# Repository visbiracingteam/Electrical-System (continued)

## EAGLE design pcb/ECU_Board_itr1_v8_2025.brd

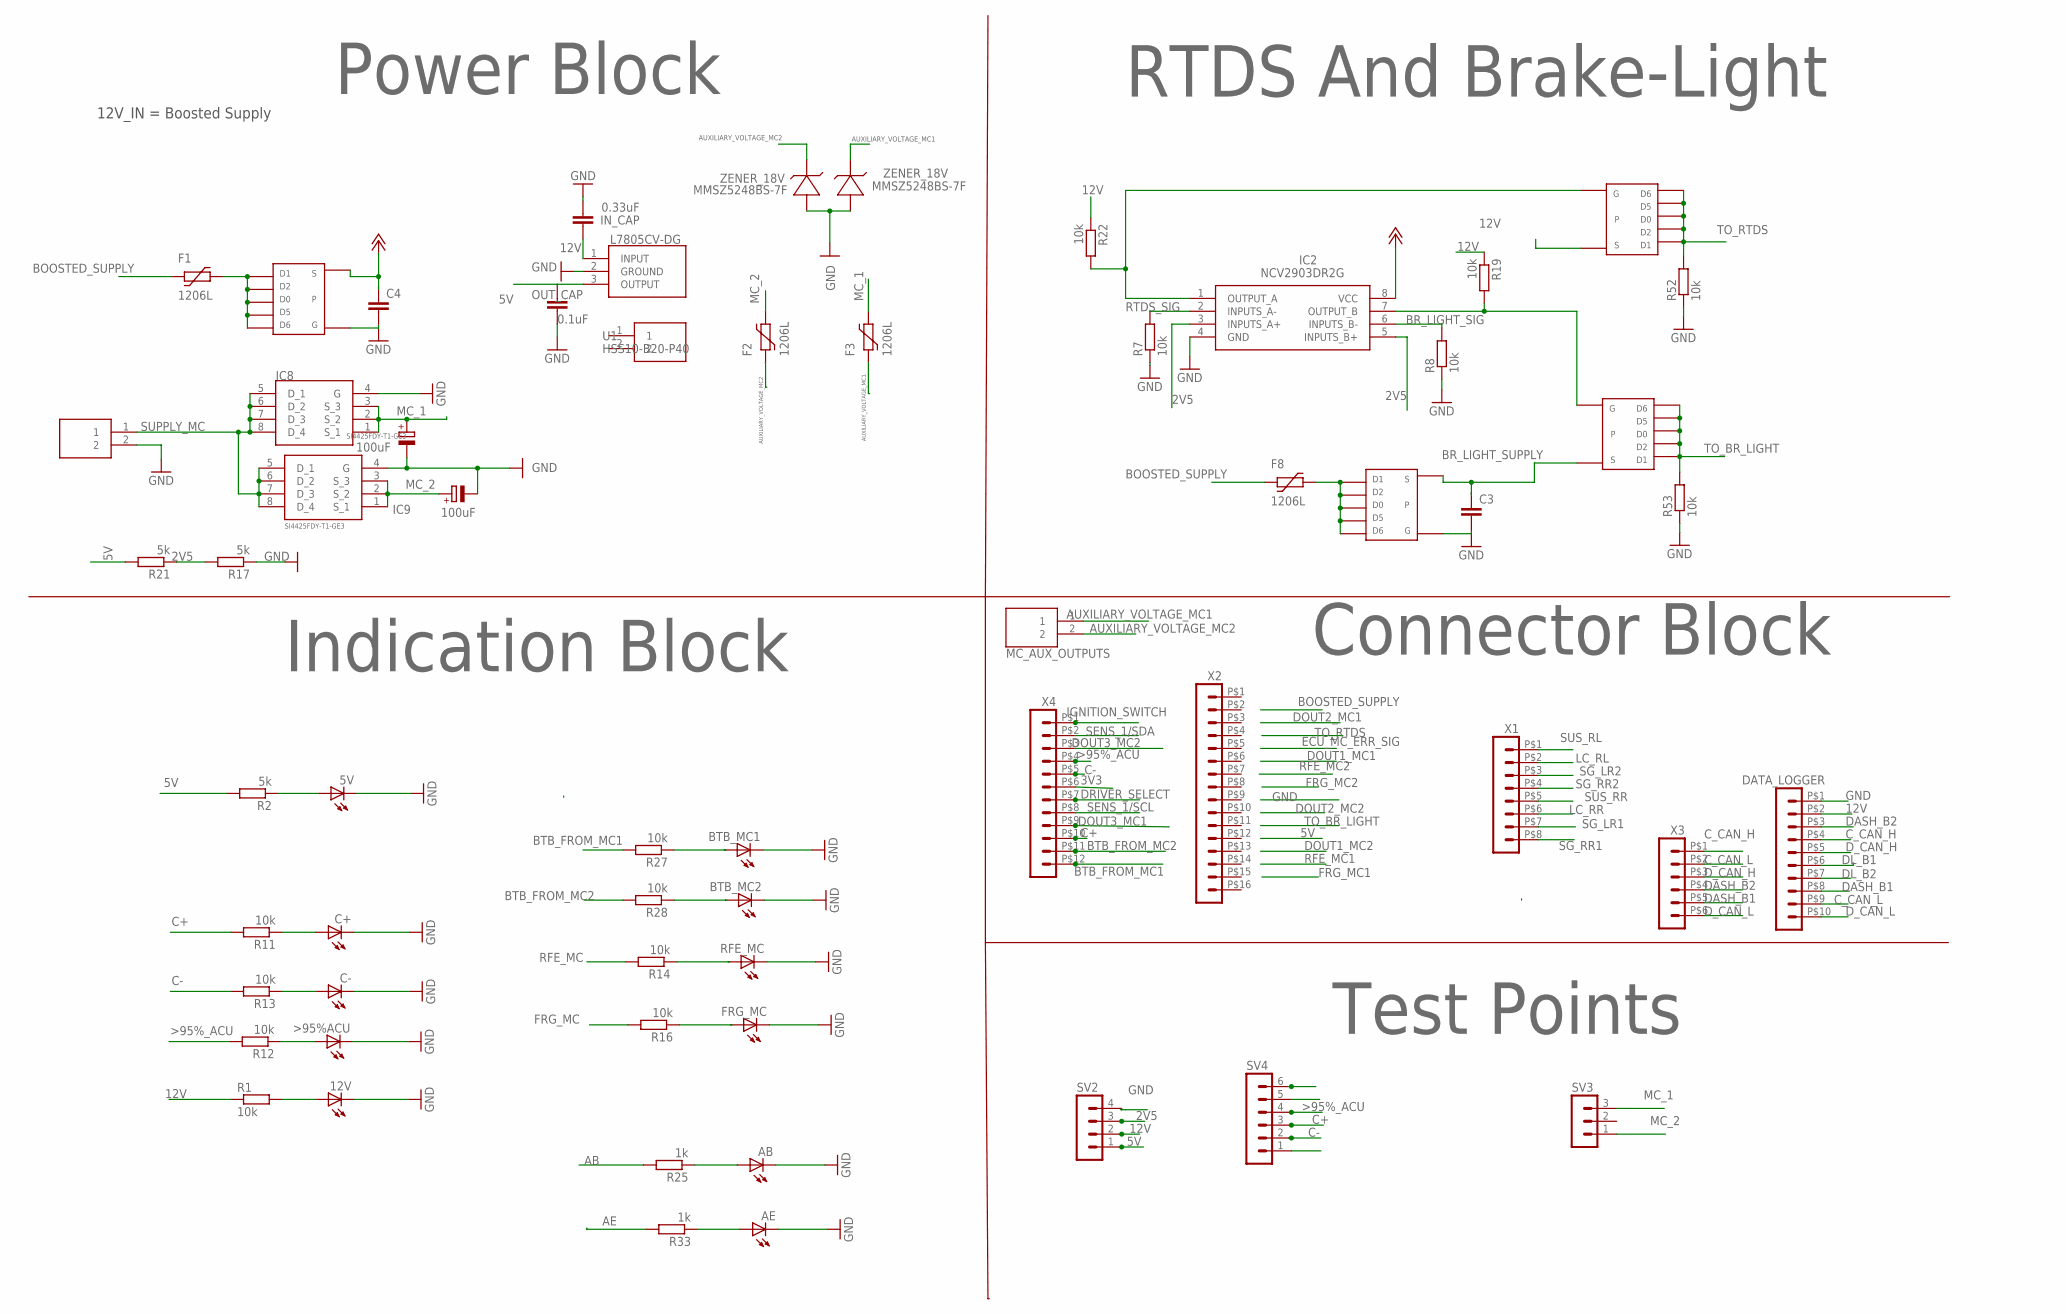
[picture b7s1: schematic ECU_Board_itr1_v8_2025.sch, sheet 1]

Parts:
5V, 12V: LED-FKIT-1206; FKIT-LED-1206
>95%ACU: LED-FKIT-1206; FKIT-LED-1206
AB: LED-FKIT-1206; FKIT-LED-1206
AE: LED-FKIT-1206; FKIT-LED-1206
BOOSTED_SUPPLY1: 172447-0002; 172447-YY02
BTB_MC1, BTB_MC2: LED-FKIT-1206; FKIT-LED-1206
C3, C4: C-EUC0805; C0805
C7, C8: 100uF; E2,5-6
C+: LED-FKIT-1206; FKIT-LED-1206
C-: LED-FKIT-1206; FKIT-LED-1206
D4, D5: ZENER; SOD123
DATA_LOGGER: HEADER_POS10_43045-1012; 43045-1012
F1, F2, F3, F8: 1206L
FRG_MC: LED-FKIT-1206; FKIT-LED-1206
IC2: NCV2903DR2G; SOIC127P600X175-8N
IC4: L7805CV-DG; TO255P460X1020X2008-3P
IC8, IC9: SI4425FDY-T1-GE3; SOIC127P600X175-8N
IN_CAP: 0.33uF; C0805
MC_AUX_OUTPUTS: 172447-0002; 172447-YY02
OUT_CAP: 0.1uF; C0805
R1, R7, R8, R11, R12, R13, R14, R16, R19, R22, R27, R28, R52, R53: 10k; R0805
R2, R17, R21: 5k; R0805
R25, R33: 1k; R0805
RFE_MC: LED-FKIT-1206; FKIT-LED-1206
SV2: MA04-1
SV3: MA03-1
SV4: MA06-1
U1: HSS10-B20-P40; HSS10B20P40
U$1, U$13, U$16, U$17: TSOP-6_PMOS
X1: HEADER_POS8_44769-0801; 44769-0801
X2: HEADER_POS16_44769-1601; 44769-1601
X3: HEADER_POS6_43045-0612; 43045-0612
X4: HEADER_POS12_44769-1201; 44769-1201

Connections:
2V5: IC2.3 (INPUTS_A+), IC2.5 (INPUTS_B+), R17.2, R21.1, SV2.3; also elsewhere on the board
3V3: SV4.1, X4.P$6 (6); also elsewhere on the board
5V: IC4.3 (OUTPUT), OUT_CAP.1, R2.2, R21.2, SV2.1; also elsewhere on the board
12V: C4.1, DATA_LOGGER.P$2 (2), IC2.8 (VCC), IC4.1 (INPUT), IN_CAP.1, R1.1, R19.1, R22.1, SV2.2, U$13.S, U$16.S; also elsewhere on the board
>95%_ACU: R12.2, SV4.4, X4.P$4 (4); also elsewhere on the board
AB: R25.2; also elsewhere on the board
AE: R33.2; also elsewhere on the board
AUXILIARY_VOLTAGE_MC1: D4.C (-), F3.P$1 (1), MC_AUX_OUTPUTS.1
AUXILIARY_VOLTAGE_MC2: D5.C (-), F2.P$1 (1), MC_AUX_OUTPUTS.2
BOOSTED_SUPPLY: F1.P$1 (1), F8.P$1 (1)
BR_LIGHT_SIG: IC2.6 (INPUTS_B-), R8.2; also elsewhere on the board
BR_LIGHT_SUPPLY: C3.1, U$1.S, U$17.S
BTB_FROM_MC1: R27.2, X4.P$12 (12); also elsewhere on the board
BTB_FROM_MC2: R28.2, X4.P$11 (11); also elsewhere on the board
C+: R11.2, SV4.3, X4.P$10 (10); also elsewhere on the board
C-: R13.2, SV4.2, X4.P$5 (5); also elsewhere on the board
C_CAN_H: DATA_LOGGER.P$4 (4), X3.P$1 (1); also elsewhere on the board
C_CAN_L: DATA_LOGGER.P$9 (9), X3.P$2 (2); also elsewhere on the board
DASH_B1: DATA_LOGGER.P$8 (8), X3.P$5 (5)
DASH_B2: DATA_LOGGER.P$3 (3), X3.P$4 (4)
DL_B1: DATA_LOGGER.P$6 (6); also elsewhere on the board
DL_B2: DATA_LOGGER.P$7 (7); also elsewhere on the board
DOUT3_MC1: SV4.5, X4.P$9 (9); also elsewhere on the board
DOUT3_MC2: SV4.6, X4.P$3 (3); also elsewhere on the board
DRIVER_SELECT: X4.P$7 (7); also elsewhere on the board
D_CAN_H: DATA_LOGGER.P$5 (5), X3.P$3 (3); also elsewhere on the board
D_CAN_L: DATA_LOGGER.P$10 (10), X3.P$6 (6); also elsewhere on the board
FRG_MC: R16.2; also elsewhere on the board
GND: 5V.C, 12V.C, >95%ACU.C, AB.C, AE.C, BOOSTED_SUPPLY1.2, BTB_MC1.C, BTB_MC2.C, C3.2, C4.2, C7.-, C8.-, C+.C, C-.C, D4.A (+), D5.A (+), DATA_LOGGER.P$1 (1), FRG_MC.C, IC2.4 (GND), IC4.2 (GROUND), IC8.4 (G), IC9.4 (G), IN_CAP.2, OUT_CAP.2, R7.1, R8.1, R17.1, R52.1, R53.1, RFE_MC.C, SV2.4, U$1.G, U$13.G; also elsewhere on the board
IGNITION_SWITCH: X4.P$1 (1); also elsewhere on the board
LC_RL: X1.P$2 (2); also elsewhere on the board
LC_RR: X1.P$6 (6); also elsewhere on the board
MC_1: C7.+, F3.P$2 (2), IC8.1 (S_1), IC8.2 (S_2), IC8.3 (S_3), SV3.3
MC_2: C8.+, F2.P$2 (2), IC9.1 (S_1), IC9.2 (S_2), IC9.3 (S_3), SV3.1
unnamed: 12V.A, R1.2
unnamed: R14.1, RFE_MC.A
unnamed: AB.A, R25.1
unnamed: FRG_MC.A, R16.1
unnamed: IC2.1 (OUTPUT_A), R22.2, U$16.G
unnamed: 5V.A, R2.1
unnamed: IC2.7 (OUTPUT_B), R19.2, U$17.G
unnamed: AE.A, R33.1
unnamed: F8.P$2 (2), U$1.1, U$1.2, U$1.5, U$1.6, U$1.D (D0)
unnamed: C+.A, R11.1
unnamed: >95%ACU.A, R12.1
unnamed: C-.A, R13.1
unnamed: BTB_MC1.A, R27.1
unnamed: BTB_MC2.A, R28.1
unnamed: F1.P$2 (2), U$13.1, U$13.2, U$13.5, U$13.6, U$13.D (D0)
RFE_MC: R14.2; also elsewhere on the board
RTDS_SIG: IC2.2 (INPUTS_A-), R7.2; also elsewhere on the board
SENS_1/SCL: X4.P$8 (8); also elsewhere on the board
SENS_1/SDA: X4.P$2 (2); also elsewhere on the board
SG_LR1: X1.P$7 (7); also elsewhere on the board
SG_LR2: X1.P$3 (3); also elsewhere on the board
SG_RR1: X1.P$8 (8); also elsewhere on the board
SG_RR2: X1.P$4 (4); also elsewhere on the board
SUPPLY_MC: BOOSTED_SUPPLY1.1, IC8.5 (D_1), IC8.6 (D_2), IC8.7 (D_3), IC8.8 (D_4), IC9.5 (D_1), IC9.6 (D_2), IC9.7 (D_3), IC9.8 (D_4)
SUS_RL: X1.P$1 (1); also elsewhere on the board
SUS_RR: X1.P$5 (5); also elsewhere on the board
TO_BR_LIGHT: R53.2, U$17.1, U$17.2, U$17.5, U$17.6, U$17.D (D0)
TO_RTDS: R52.2, U$16.1, U$16.2, U$16.5, U$16.6, U$16.D (D0)

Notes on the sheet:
Power Block
RTDS And Brake-Light
Indication Block
Connector Block
Test Points
12V_IN = Boosted Supply

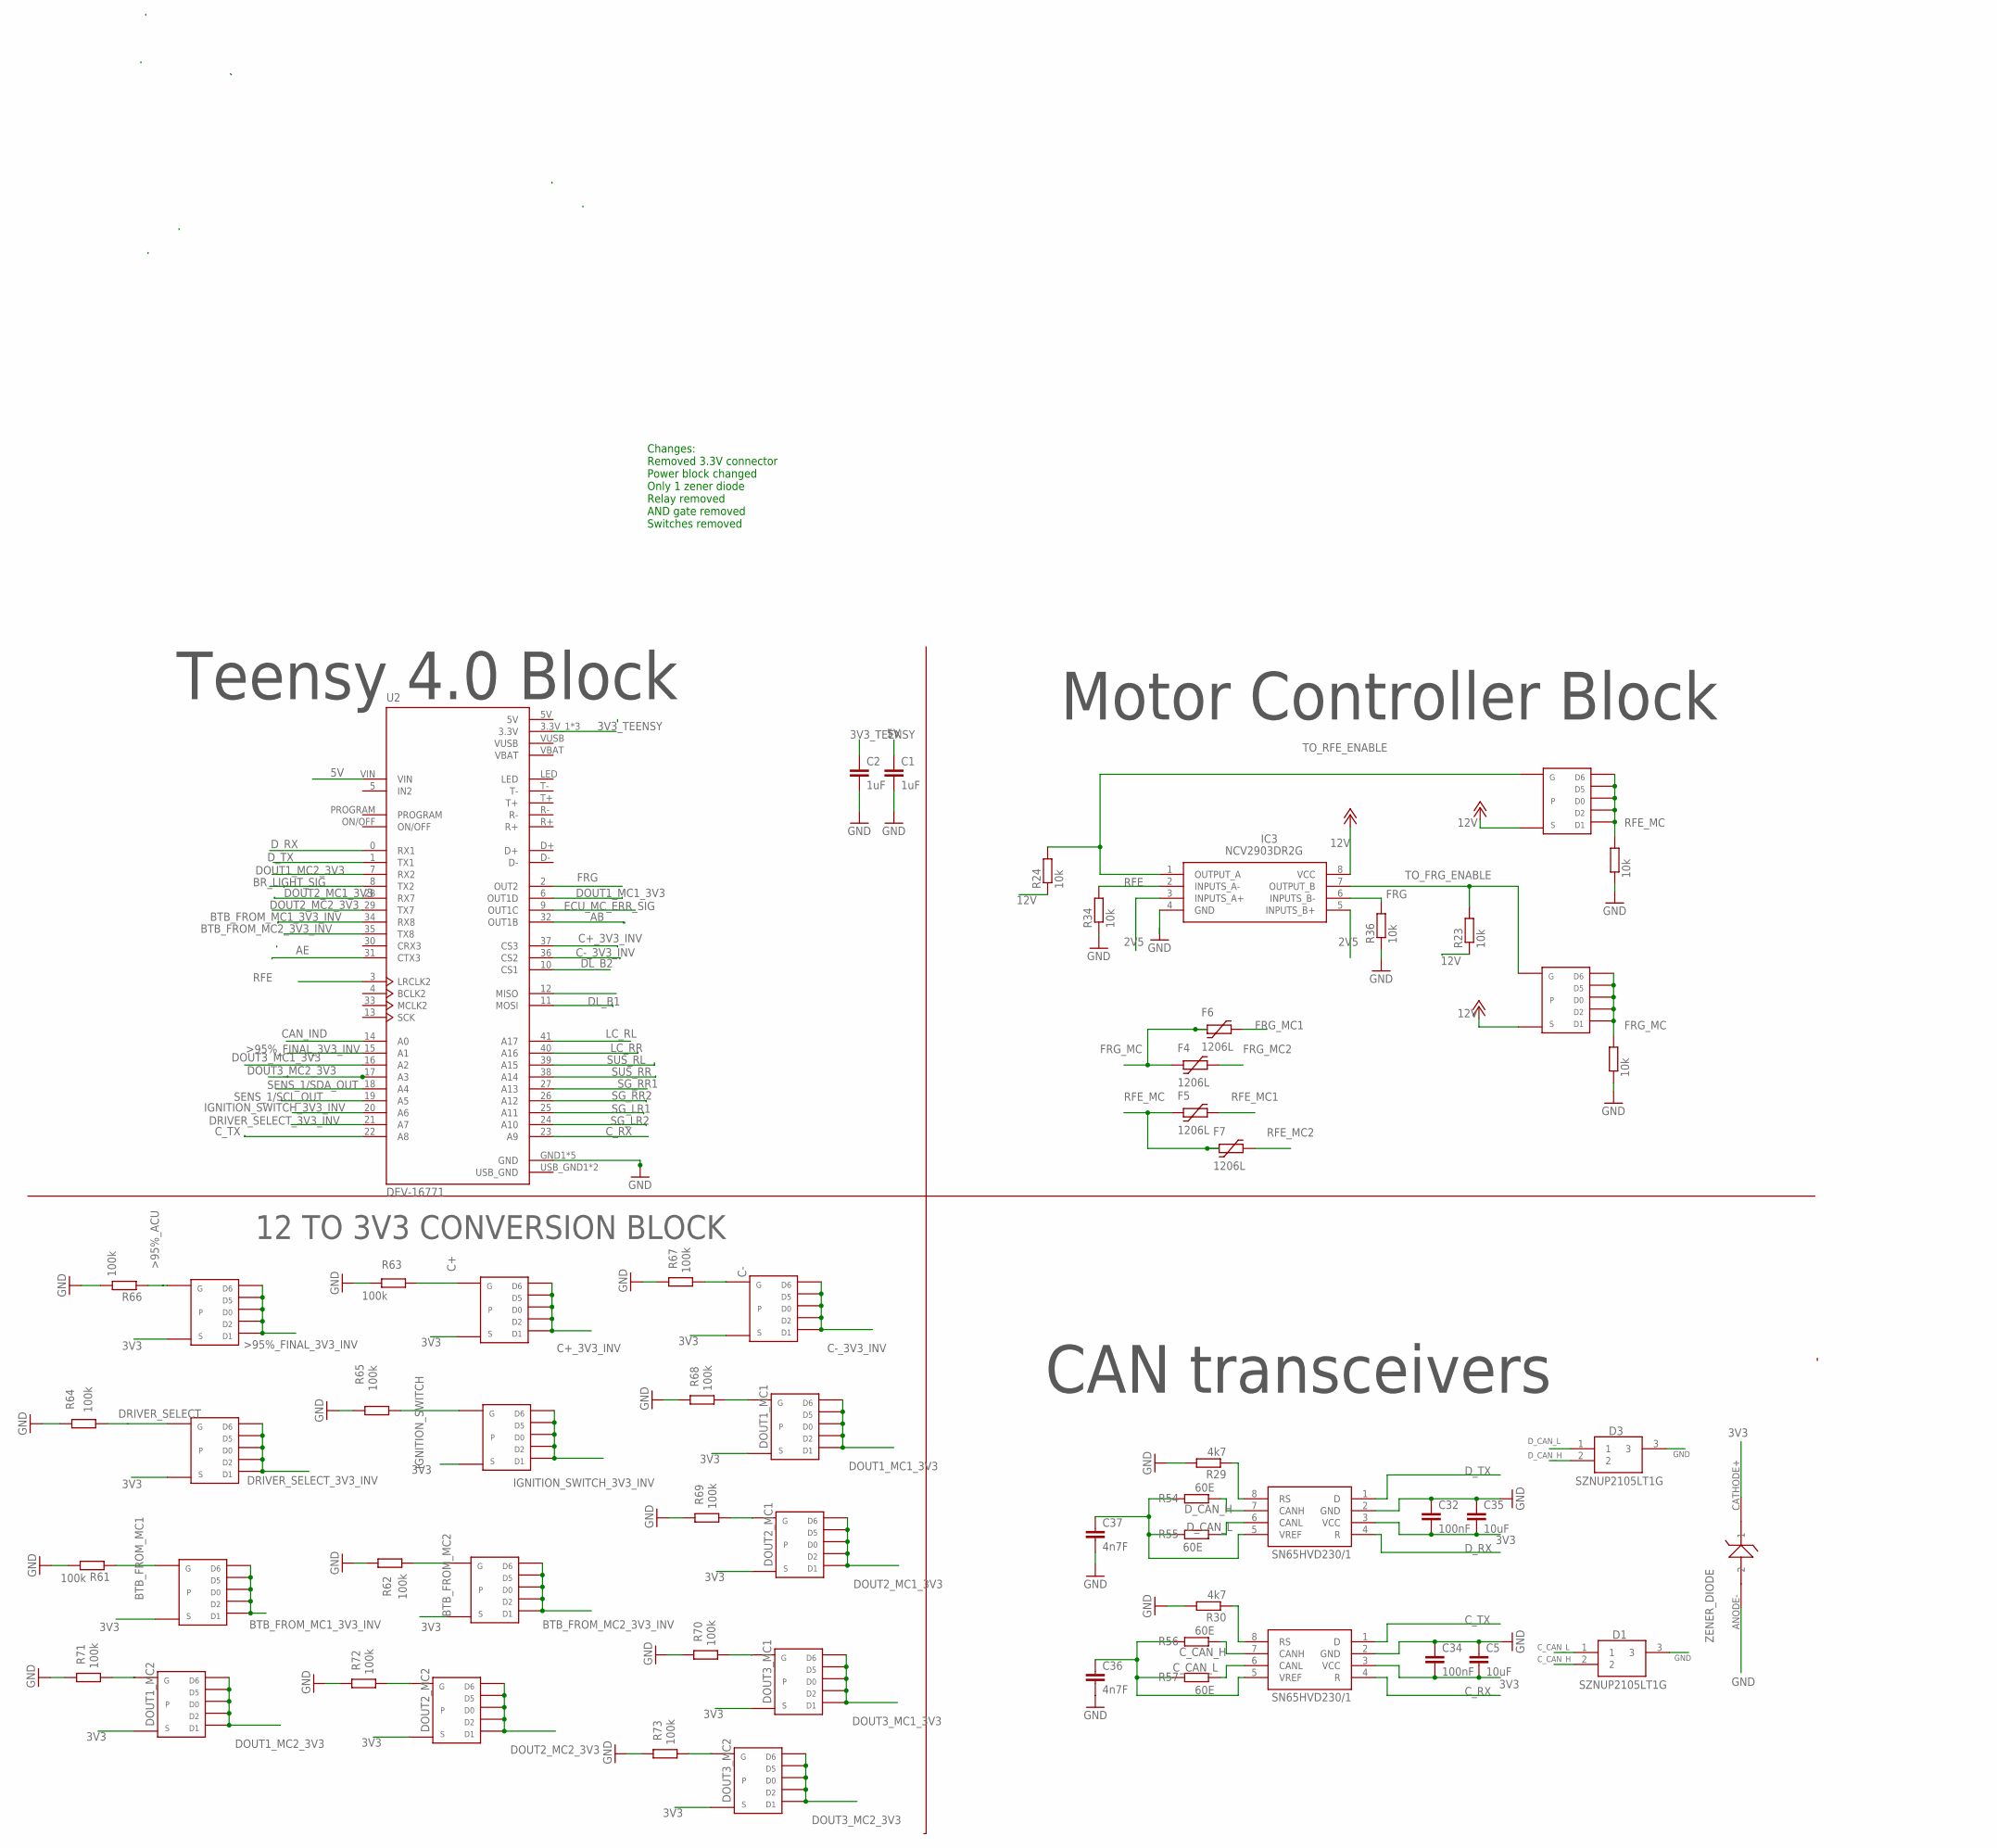
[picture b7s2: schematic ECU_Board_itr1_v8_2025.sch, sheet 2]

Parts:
C1, C2: 1uF; C0805
C5, C35: 10uF; C0805
C32, C34: 100nF; C0805
C36, C37: 4n7F; C0805
D1, D3: SZNUP2105LT1G; SOT96P237X111-3N
F4, F5, F6, F7: 1206L
IC3: NCV2903DR2G; SOIC127P600X175-8N
R23, R24, R31, R32, R34, R36: 10k; R0805
R29, R30: 4k7; R0805
R54, R55, R56, R57: 60E; R0805
R61, R62, R63, R64, R65, R66, R67, R68, R69, R70, R71, R72, R73: 100k; R0805
U2: DEV-16771; MODULE_DEV-16771
U$7, U$8: SN65HVD230/1; SO8
U$14, U$15, U$24, U$25, U$26, U$27, U$28, U$29, U$30, U$31, U$32, U$33, U$34, U$35, U$36: TSOP-6_PMOS
U$20: ZENER_DIODE; SOD323HE

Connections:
2V5: IC3.3 (INPUTS_A+), IC3.5 (INPUTS_B+); also elsewhere on the board
3V3: C5.2, C32.2, C34.2, C35.2, U$7.3 (VCC), U$8.3 (VCC), U$20.CATHODE+ (1), U$24.S, U$25.S, U$26.S, U$27.S, U$28.S, U$29.S, U$30.S, U$31.S, U$32.S, U$33.S, U$34.S, U$35.S, U$36.S; also elsewhere on the board
3V3_TEENSY: C2.1, U2.3.3V_1 (3.3V), U2.3.3V_2 (3.3V), U2.3.3V_3 (3.3V); also elsewhere on the board
5V: C1.1, U2.5V, U2.VIN; also elsewhere on the board
12V: IC3.8 (VCC), R23.1, R24.1, U$14.S, U$15.S; also elsewhere on the board
>95%_ACU: R66.1, U$25.G; also elsewhere on the board
>95%_FINAL_3V3_INV: U2.15 (A1), U$25.1, U$25.2, U$25.5, U$25.6, U$25.D (D0)
AB: U2.32 (OUT1B); also elsewhere on the board
AE: U2.31 (CTX3); also elsewhere on the board
BR_LIGHT_SIG: U2.8 (TX2); also elsewhere on the board
BTB_FROM_MC1: R61.1, U$27.G; also elsewhere on the board
BTB_FROM_MC1_3V3_INV: U2.34 (RX8), U$27.1, U$27.2, U$27.5, U$27.6, U$27.D (D0)
BTB_FROM_MC2: R62.1, U$26.G; also elsewhere on the board
BTB_FROM_MC2_3V3_INV: U2.35 (TX8), U$26.1, U$26.2, U$26.5, U$26.6, U$26.D (D0)
C+: R63.1, U$24.G; also elsewhere on the board
C+_3V3_INV: U2.37 (CS3), U$24.1, U$24.2, U$24.5, U$24.6, U$24.D (D0)
C-: R67.1, U$30.G; also elsewhere on the board
C-_3V3_INV: U2.36 (CS2), U$30.1, U$30.2, U$30.5, U$30.6, U$30.D (D0)
CAN_IND: U2.14 (A0)
C_CAN_H: D1.2, R56.1, U$7.7 (CANH); also elsewhere on the board
C_CAN_L: D1.1, R57.1, U$7.6 (CANL); also elsewhere on the board
C_RX: U2.23 (A9), U$7.4 (R)
C_TX: U2.22 (A8), U$7.1 (D)
DL_B1: U2.11 (MOSI); also elsewhere on the board
DL_B2: U2.10 (CS1); also elsewhere on the board
DOUT1_MC1: R68.1, U$31.G
DOUT1_MC1_3V3: U2.6 (OUT1D), U$31.1, U$31.2, U$31.5, U$31.6, U$31.D (D0)
DOUT1_MC2: R71.1, U$34.G
DOUT1_MC2_3V3: U2.7 (RX2), U$34.1, U$34.2, U$34.5, U$34.6, U$34.D (D0)
DOUT2_MC1: R69.1, U$32.G
DOUT2_MC1_3V3: U2.28 (RX7), U$32.1, U$32.2, U$32.5, U$32.6, U$32.D (D0)
DOUT2_MC2: R72.1, U$35.G
DOUT2_MC2_3V3: U2.29 (TX7), U$35.1, U$35.2, U$35.5, U$35.6, U$35.D (D0)
DOUT3_MC1: R70.1, U$33.G; also elsewhere on the board
DOUT3_MC1_3V3: U2.16 (A2), U$33.1, U$33.2, U$33.5, U$33.6, U$33.D (D0)
DOUT3_MC2: R73.1, U$36.G; also elsewhere on the board
DOUT3_MC2_3V3: U2.17 (A3), U$36.1, U$36.2, U$36.5, U$36.6, U$36.D (D0)
DRIVER_SELECT: R64.1, U$29.G; also elsewhere on the board
DRIVER_SELECT_3V3_INV: U2.21 (A7), U$29.1, U$29.2, U$29.5, U$29.6, U$29.D (D0)
D_CAN_H: D3.2, R54.1, U$8.7 (CANH); also elsewhere on the board
D_CAN_L: D3.1, R55.1, U$8.6 (CANL); also elsewhere on the board
D_RX: U2.0 (RX1), U$8.4 (R)
D_TX: U2.1 (TX1), U$8.1 (D)
ECU_MC_ERR_SIG: U2.9 (OUT1C)
FRG: IC3.6 (INPUTS_B-), R36.2, U2.2 (OUT2)
FRG_MC: F4.P$1 (1), F6.P$1 (1), R32.2, U$15.1, U$15.2, U$15.5, U$15.6, U$15.D (D0); also elsewhere on the board
FRG_MC1: F6.P$2 (2)
FRG_MC2: F4.P$2 (2)
GND: C1.2, C2.2, C5.1, C32.1, C34.1, C35.1, C36.2, C37.2, D1.3, D3.3, IC3.4 (GND), R29.2, R30.2, R31.1, R32.1, R34.1, R36.1, R61.2, R62.2, R63.2, R64.2, R65.2, R66.2, R67.2, R68.2, R69.2, R70.2, R71.2, R72.2, R73.2, U2.GND1 (GND), U2.GND2 (GND), U2.GND3 (GND), U2.GND4 (GND), U2.GND5 (GND), U$7.2 (GND), U$8.2 (GND), U$20.ANODE- (2); also elsewhere on the board
IGNITION_SWITCH: R65.1, U$28.G; also elsewhere on the board
IGNITION_SWITCH_3V3_INV: U2.20 (A6), U$28.1, U$28.2, U$28.5, U$28.6, U$28.D (D0)
LC_RL: U2.41 (A17); also elsewhere on the board
LC_RR: U2.40 (A16); also elsewhere on the board
unnamed: R29.1, U$8.8 (RS)
unnamed: C37.1, R54.2, R55.2, U$8.5 (VREF)
unnamed: C36.1, R56.2, R57.2, U$7.5 (VREF)
unnamed: R30.1, U$7.8 (RS)
RFE: IC3.2 (INPUTS_A-), R34.2, U2.3 (LRCLK2)
RFE_MC: F5.P$1 (1), F7.P$1 (1), R31.2, U$14.1, U$14.2, U$14.5, U$14.6, U$14.D (D0); also elsewhere on the board
RFE_MC1: F5.P$2 (2)
RFE_MC2: F7.P$2 (2)
RTDS_SIG: U2.12 (MISO); also elsewhere on the board
SENS_1/SCL_OUT: U2.19 (A5); also elsewhere on the board
SENS_1/SDA_OUT: U2.18 (A4); also elsewhere on the board
SG_LR1: U2.25 (A11); also elsewhere on the board
SG_LR2: U2.24 (A10); also elsewhere on the board
SG_RR1: U2.27 (A13); also elsewhere on the board
SG_RR2: U2.26 (A12); also elsewhere on the board
SUS_RL: U2.39 (A15); also elsewhere on the board
SUS_RR: U2.38 (A14); also elsewhere on the board
TO_FRG_ENABLE: IC3.7 (OUTPUT_B), R23.2, U$15.G
TO_RFE_ENABLE: IC3.1 (OUTPUT_A), R24.2, U$14.G
USB_GND: U2.USB_GND1 (USB_GND), U2.USB_GND2 (USB_GND)

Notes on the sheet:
CAN transceivers
Motor Controller Block
Teensy 4.0 Block
Changes: Removed 3.3V connector Power block changed Only 1 zener diode Relay removed AND gate removed Switches removed
12 TO 3V3 CONVERSION BLOCK

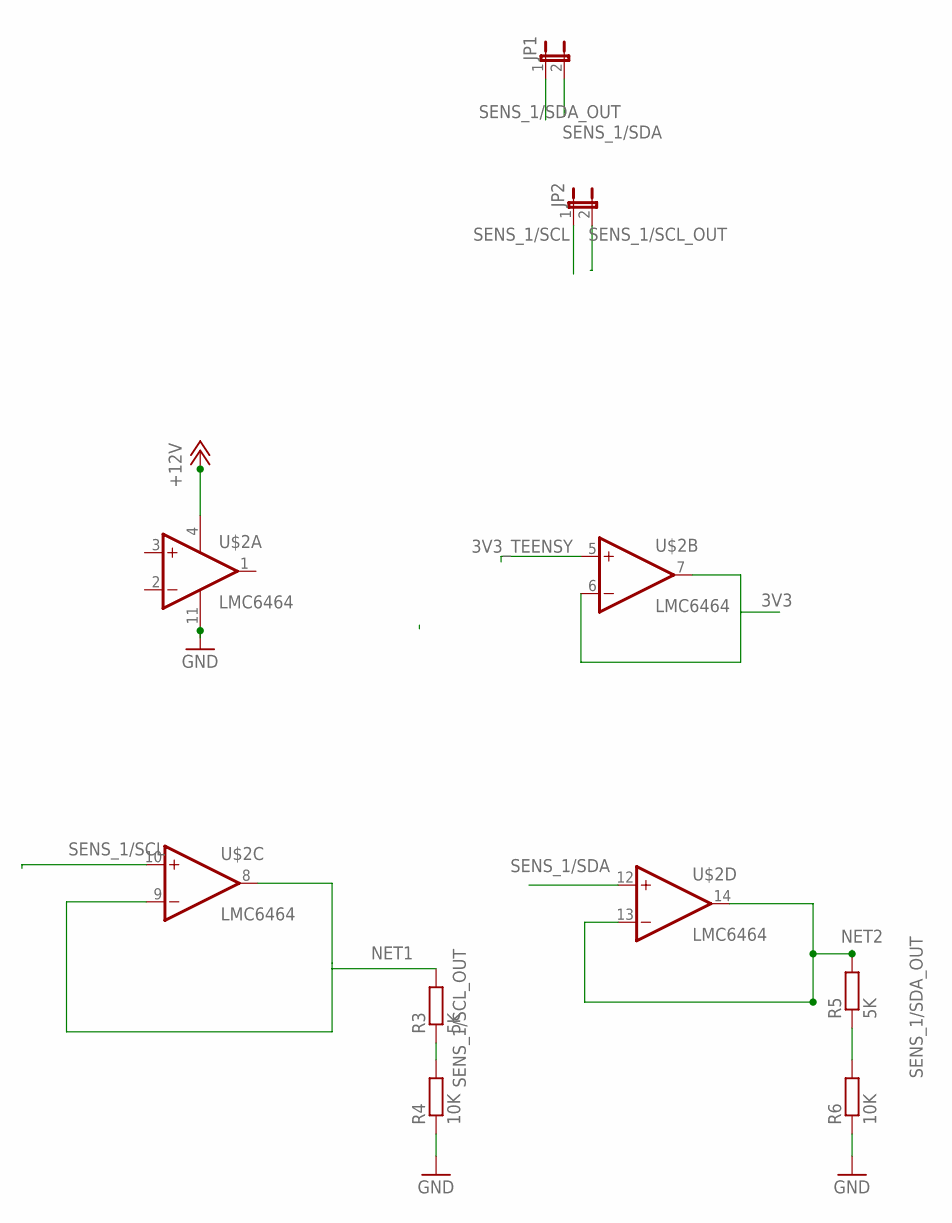
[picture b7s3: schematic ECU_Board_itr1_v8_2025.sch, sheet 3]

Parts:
JP1, JP2: JP1E; JP1
R3, R5: 5K; R0805
R4, R6: 10K; R0805
U$2: LMC6464; SO14_LONGPADS

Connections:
3V3: U$2.6 (-IN), U$2.7 (OUT); also elsewhere on the board
3V3_TEENSY: U$2.5 (+IN); also elsewhere on the board
+12V: U$2.4 (V+)
GND: R4.1, R6.1, U$2.11 (V-); also elsewhere on the board
NET1: R3.2, U$2.8 (OUT), U$2.9 (-IN)
NET2: R5.2, U$2.13 (-IN), U$2.14 (OUT)
SENS_1/SCL: JP2.1, U$2.10 (+IN); also elsewhere on the board
SENS_1/SCL_OUT: JP2.2, R3.1, R4.2; also elsewhere on the board
SENS_1/SDA: JP1.2, U$2.12 (+IN); also elsewhere on the board
SENS_1/SDA_OUT: JP1.1, R5.1, R6.2; also elsewhere on the board

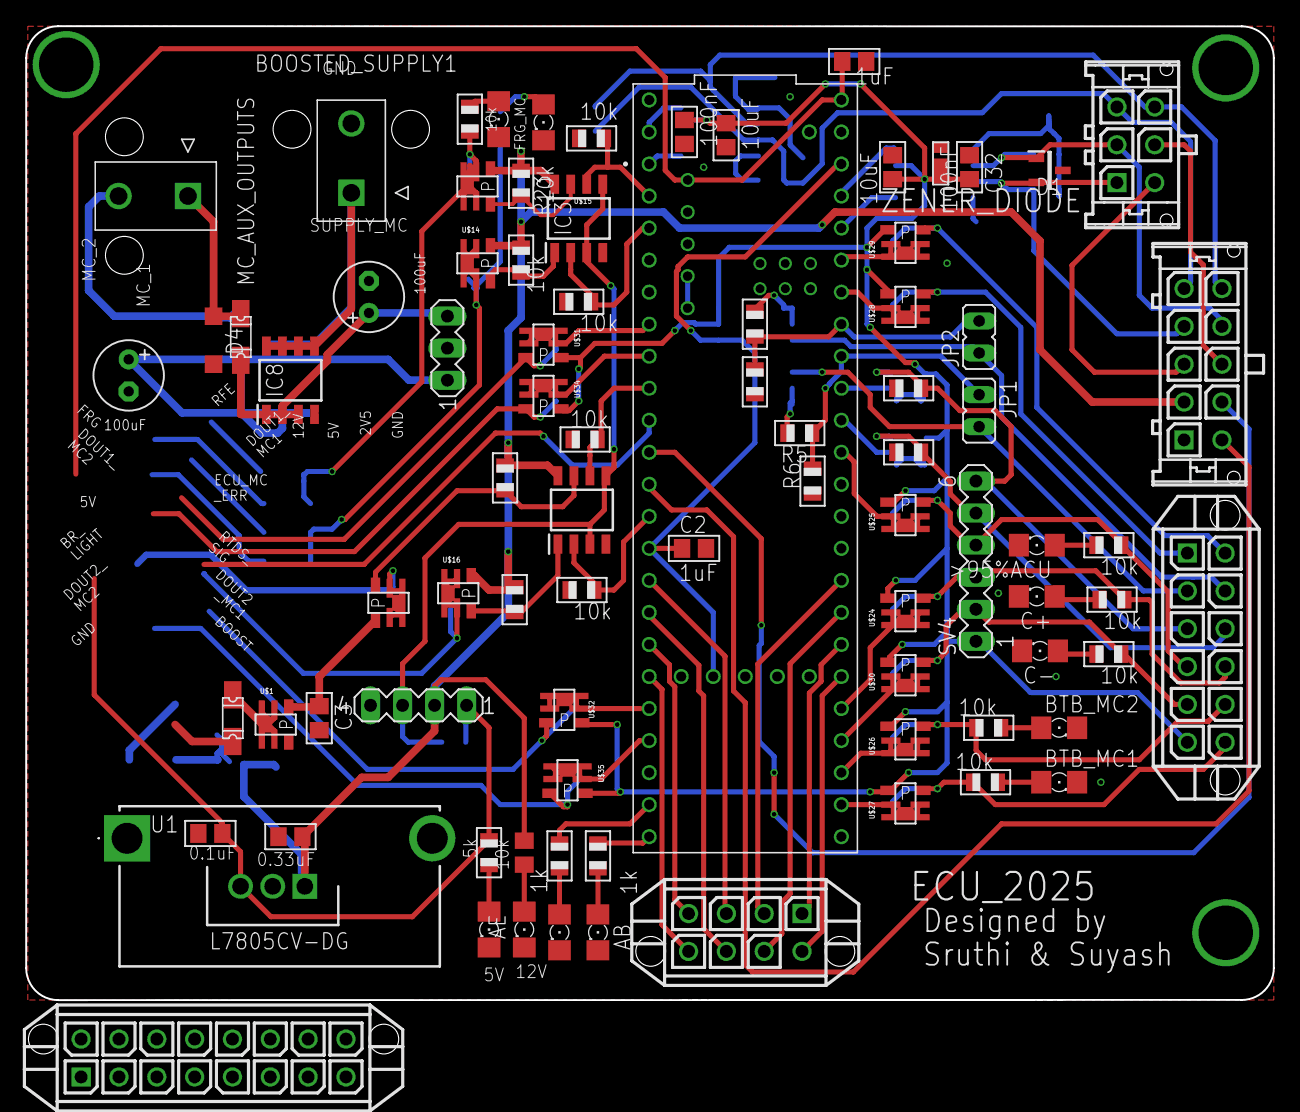
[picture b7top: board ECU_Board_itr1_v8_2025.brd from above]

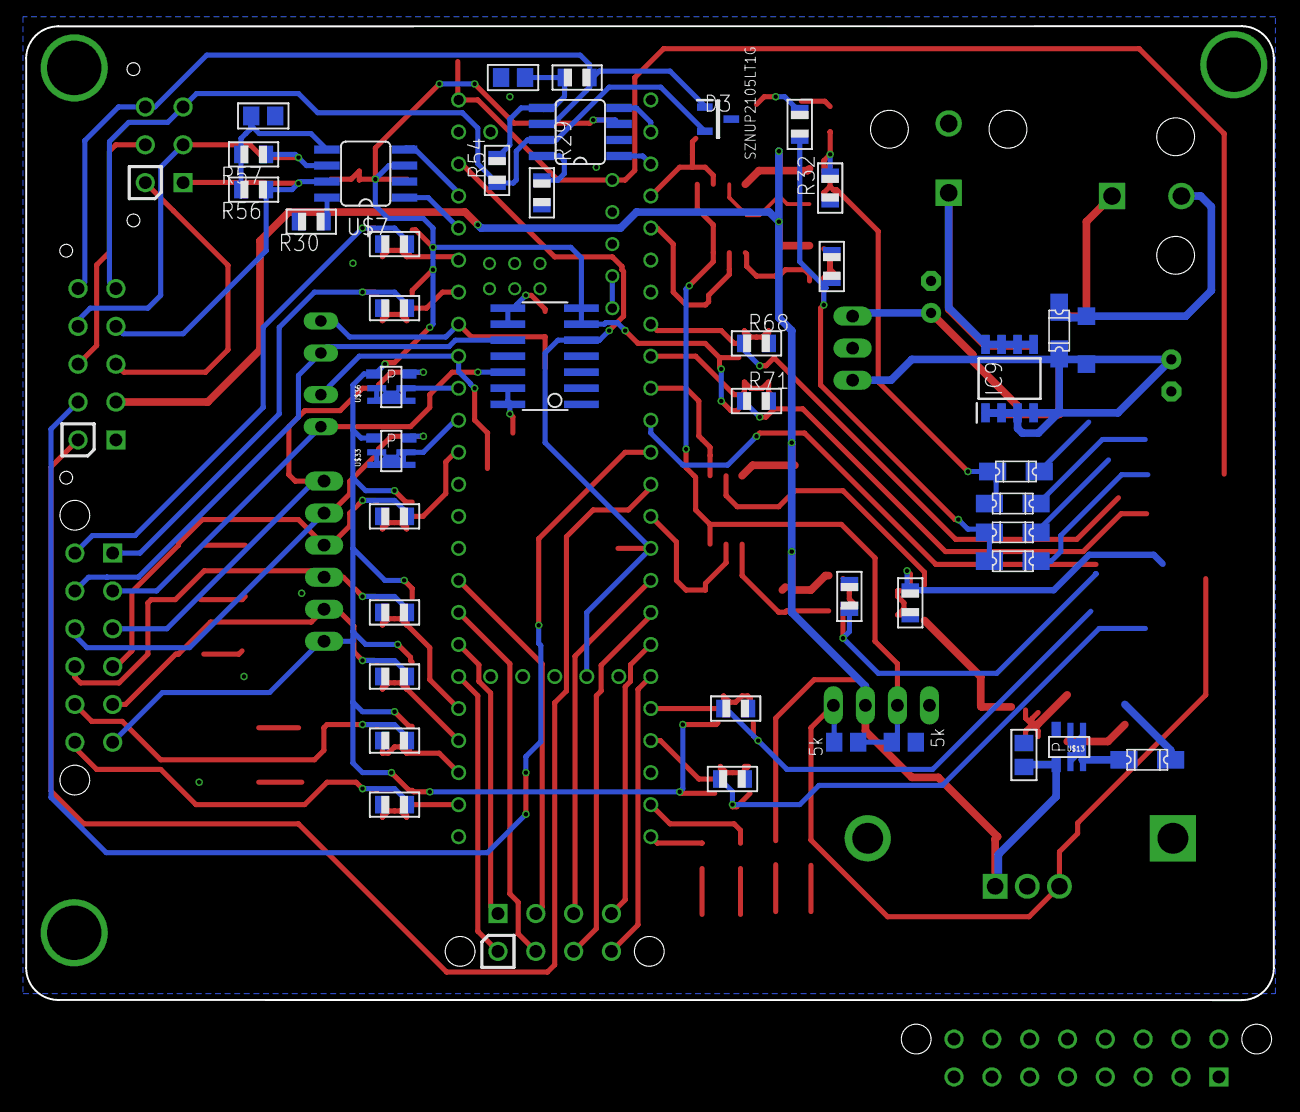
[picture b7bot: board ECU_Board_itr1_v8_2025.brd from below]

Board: 2 copper layers, 98.9 x 77.2 mm, 127 parts (42 on the bottom side), 97 nets.

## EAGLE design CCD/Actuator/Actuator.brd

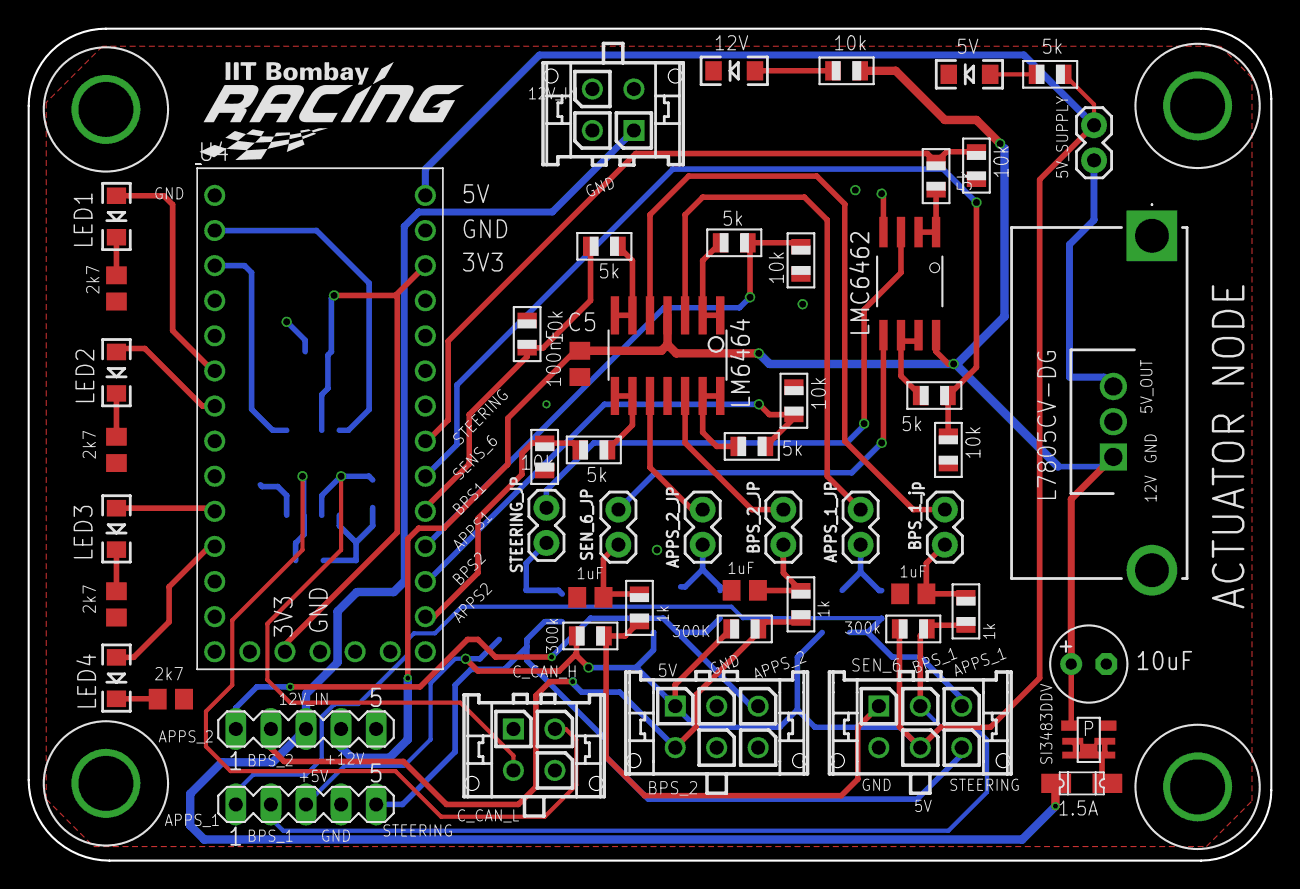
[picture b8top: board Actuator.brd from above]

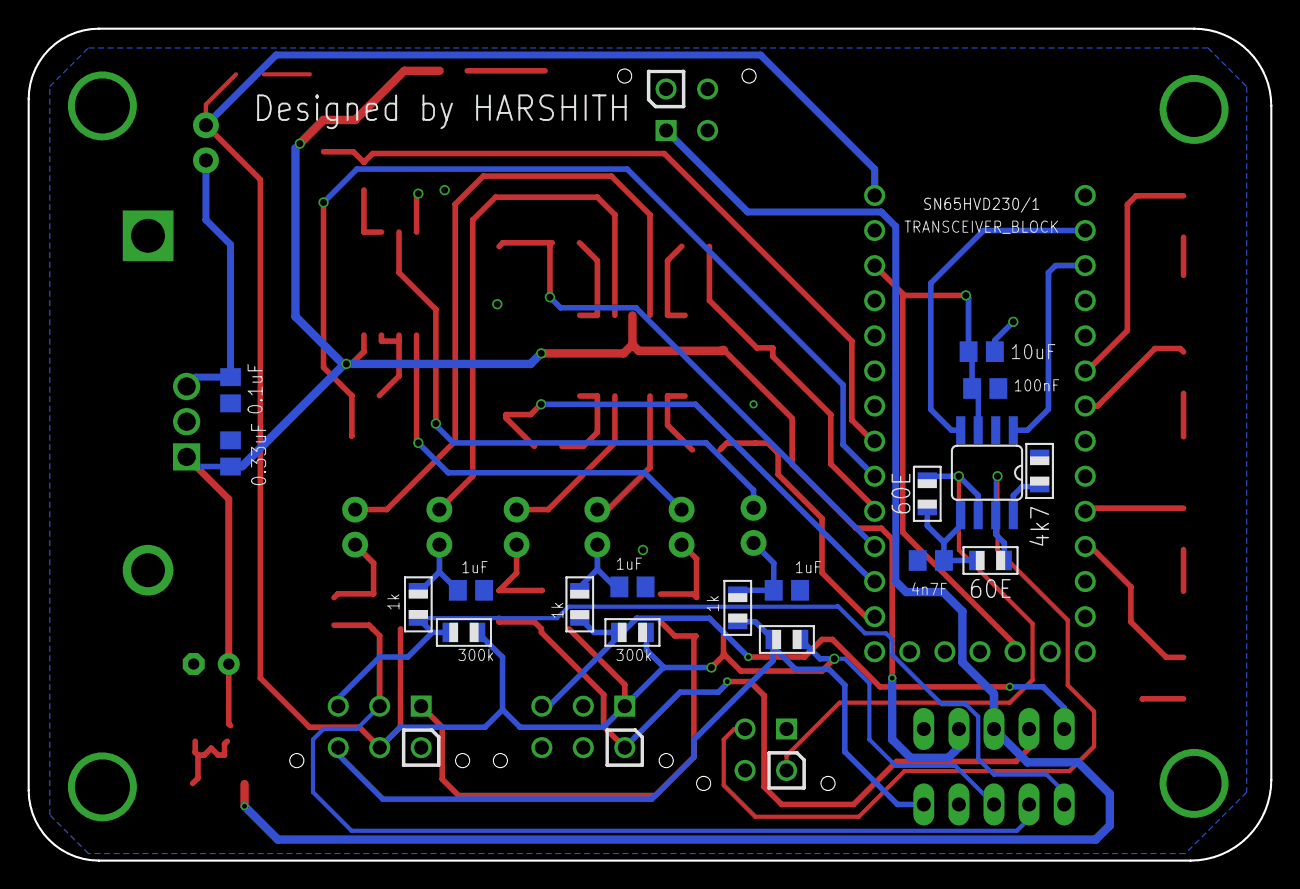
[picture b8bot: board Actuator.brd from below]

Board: 2 copper layers, 89.9 x 60.2 mm, 74 parts (18 on the bottom side), 53 nets.

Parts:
5V_LED, 12V_LED: LED-1206
APPS_1_JP: 1X02
APPS_2_JP: APPS_2_JP; 1X02
BPS_1_JP: BPS_1_jp; 1X02
BPS_2_JP: BPS_2_JP; 1X02
C1: 4n7F; C0805
C2: 10uF; E2,5-6
C3, C5: 100nF; C0805
C4: 10uF; C0805
F2: 1206L
IC3: L7805CV-DG; TO255P460X1020X2008-3P
IN_CAP: 0.33uF; C0805
J7: 1X02
LED1, LED2, LED3, LED4: LED-1206
LM6462: LMC6462; S08
LM6464: LMC6464; SO14_LONGPADS
OUT_CAP: 0.1uF; C0805
OUT_CAP1, OUT_CAP2, OUT_CAP3, OUT_CAP4: 1uF; C0805
R1, R2, R3, R4: 2k7; R0805
R5: 4k7; R0805
R6, R25: 60E; R0805
R7, R8, R38, R43, R50: 1k; R0805
R9, R15, R17, R29, R31, R33, R53: 10k; R0805
R10, R16, R18, R30, R32, R34, R54: 5k; R0805
R23, R24, R39, R42, R49: 300k; R0805
R41: 300K; R0805
R_41: 1k; R0805
S-2, S-6: 1uF; C0805
SENSOR_CAN_TRANSCEIVER: SN65HVD230/1; SO8
SEN_6_JP: SEN_6_JP; 1X02
STEERING_JP: STEERING_JP; 1X02
SUPPLY_TEST1, SUPPLY_TEST2: MA05-1
U3: HSS10-B20-P40; HSS10B20P40
U4: DEV-15583; MODULE_DEV-15583
U$1: TSOP-6_PMOS
U$5: RACING_LOGO_290MIL
X1, X4: 43045-0412
X2, X3: 43045-0612

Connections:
3V3: C3.2, C4.2, SENSOR_CAN_TRANSCEIVER.3, U4.3.3V_1, U4.3.3V_2
5V_OUT: IC3.3, J7.2, OUT_CAP.1
12V_IN: F2.P$1, SUPPLY_TEST2.3, X1.P$1
+5V: J7.1, R10.1, R23.2, R24.2, R39.2, R41.2, R42.2, R49.2, SUPPLY_TEST1.3, U4.VIN, X2.P$5, X3.P$1
+12V: C2.+, C5.1, IC3.1, IN_CAP.1, LM6462.8, LM6464.4, R9.2, SUPPLY_TEST2.4, U$1.S
APPS_1: R49.1, R50.2, SUPPLY_TEST1.1, X2.P$3
APPS_1_IN: R53.1, R54.1, U4.16
APPS_1_JP: APPS_1_JP.2, LM6464.3
APPS_2: R42.1, R43.1, SUPPLY_TEST2.1, X3.P$3
APPS_2_IN: R31.1, R32.1, U4.14
APPS_2_JP: APPS_2_JP.2, LM6464.10
BPS_1: R39.1, R_41.2, SUPPLY_TEST1.2, X2.P$2
BPS_1_IN: R29.1, R30.1, U4.17
BPS_1_JP: BPS_1_JP.2, LM6464.5
BPS_2: R38.1, R41.1, SUPPLY_TEST2.2, X3.P$4
BPS_2_IN: R33.1, R34.1, U4.15
BPS_2_JP: BPS_2_JP.2, LM6464.12
C_CAN_H: R6.2, SENSOR_CAN_TRANSCEIVER.7, X4.P$2
C_CAN_L: R25.2, SENSOR_CAN_TRANSCEIVER.6, X4.P$3
C_CAN_RX: SENSOR_CAN_TRANSCEIVER.4, U4.0
C_CAN_TX: SENSOR_CAN_TRANSCEIVER.1, U4.1
GND: 5V_LED.C, 12V_LED.C, C1.2, C2.-, C3.1, C4.1, C5.2, IC3.2, IN_CAP.2, LM6462.4, LM6464.11, OUT_CAP.2, OUT_CAP1.2, OUT_CAP2.2, OUT_CAP3.2, OUT_CAP4.2, R1.1, R2.1, R3.1, R4.1, R5.1, R15.1, R17.1, R29.2, R31.2, R33.2, R53.2, S-2.2, S-6.2, SENSOR_CAN_TRANSCEIVER.2, SUPPLY_TEST1.4, U4.G1, U$1.G, X1.P$4, X2.P$4, X3.P$2
unnamed: R8.1, S-2.1, STEERING_JP.1
unnamed: 5V_LED.A, R10.2
unnamed: R5.2, SENSOR_CAN_TRANSCEIVER.8
unnamed: LED1.A, U4.4
unnamed: LED2.A, U4.5
unnamed: C1.1, R6.1, R25.1, SENSOR_CAN_TRANSCEIVER.5
unnamed: LED3.A, U4.8
unnamed: F2.P$2, U$1.1, U$1.2, U$1.5, U$1.6, U$1.D
unnamed: LM6462.1, LM6462.2, R16.2
unnamed: LED4.A, U4.9
unnamed: LED3.C, R4.2
unnamed: LED4.C, R1.2
unnamed: LED2.C, R3.2
unnamed: 12V_LED.A, R9.1
unnamed: LED1.C, R2.2
unnamed: LM6462.6, LM6462.7, R18.2
unnamed: BPS_1_JP.1, OUT_CAP1.1, R_41.1
unnamed: LM6464.8, LM6464.9, R32.2
unnamed: LM6464.6, LM6464.7, R30.2
unnamed: LM6464.13, LM6464.14, R34.2
unnamed: APPS_2_JP.1, OUT_CAP4.1, R43.2
unnamed: BPS_2_JP.1, OUT_CAP2.1, R38.2
unnamed: APPS_1_JP.1, OUT_CAP3.1, R50.1
unnamed: LM6464.1, LM6464.2, R54.2
SEN_6: R7.2, R24.1, X2.P$1
SEN_6_IN: R17.2, R18.1, U4.18
SEN_6_JP: LM6462.5, SEN_6_JP.2
SEN_6_LPF: R7.1, S-6.1, SEN_6_JP.1
STEERING: R8.2, R23.1, SUPPLY_TEST1.5, X2.P$6
STEERING_IN: R15.2, R16.1, U4.19
STEERING_JP: LM6462.3, STEERING_JP.2

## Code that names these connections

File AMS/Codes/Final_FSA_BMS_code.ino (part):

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

// defined by me
#define BMS_FLT_3V3 18  // PIN 18 ( A4 ) selected as BMS ERROR pin on teensy can check on master
#define FAN_MBED 19     // FAN mbed signal to ACU
#define CH_EN_MBED 22   // charger enable signal to ACU
#define PEC_ERR_PIN 9   // to switch error state led on master
#define VOLT_ERR_PIN 7  // to switch error state led on master
#define TEMP_ERR_PIN 8  // to switch error state led on master

#define voltTimer 400  // Time for voltage loop to go on in its error checking mode
#define tempTimer 900  // Time for temperature loop to go on in its error checking mode
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
#define UI_BUFFER_SIZE 64

#define RES 30000  // Resistor divider for BATP and BATM
#define RES_SUM 6520000
#define POT_DIV_BPM 76.5  // Voltage Multiplier for BPM
// set sense resistor here
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  digitalWrite(LTCDEF_GPO, HIGH);
  pinMode(LTCDEF_GPO, OUTPUT);

  pinMode(PEC_ERR_PIN, OUTPUT);
  pinMode(VOLT_ERR_PIN, OUTPUT);
  pinMode(TEMP_ERR_PIN, OUTPUT);
  pinMode(BMS_FLT_3V3, OUTPUT);  // Bpin defined for sending signal to ACU for BMS error
  pinMode(FAN_MBED, OUTPUT);
  pinMode(CH_EN_MBED, OUTPUT);


  initialiseSDcard();
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        break;
      case 1:
        if (tempFlag) {
          digitalWriteFast(TEMP_ERR_PIN, HIGH);
        } else {
          digitalWriteFast(TEMP_ERR_PIN, LOW);
        }
        break;
      case 2:
        if (voltFlag && tempFlag) {
          digitalWriteFast(VOLT_ERR_PIN, HIGH);
          digitalWriteFast(TEMP_ERR_PIN, HIGH);
        }
        break;
    }
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
  REG  |  BIT_7  |  BIT_6  |  BIT_5  |  BIT_4  |  BIT_3  |  BIT_2  |  BIT_1  |  BIT_0  |
----------------------------------------------------------------------------------------
CFGAR0 |  GPIO5  |  GPIO4  |  GPIO3  |  GPIO2  |  GPIO1  |  REFON  |   DTEN  | ADC_OPT |

here in the code cellMonDat[i * 6 + 0] represents the CFGRA0 registers byte of the (i + 1)th slaves
 
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
  REG  |  BIT_7  |  BIT_6  |  BIT_5  |  BIT_4  |  BIT_3  |  BIT_2  |  BIT_1  |  BIT_0  |
----------------------------------------------------------------------------------------
CFGBR0 |  DCC16  |  DCC15  |  DCC14  |  DCC13  |  GPIO9  |  GPIO8  |  GPIO7  |  GPIO6  |

here in the code cellMonDat[i * 6 + 0] represents the CFGBR0 registers byte of the (i + 1)th slaves

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
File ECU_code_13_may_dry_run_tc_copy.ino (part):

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#define dash_sent_id 169

//Pin mappinigs
const int rtds_sig = 4;
const int br_light = 2;
const int ignition_sig = 20;
const int dr_select = 21;
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const int AD = 5;
const int AE = 9;
const int c_plus = 18;
const int frg = 6;
const int rfe = 7;
double Kp=10, Ki=0, Kd=0;
double input, output, setPoint;
PID myPID(&input, &output, &setPoint, Kp, Ki, Kd, DIRECT);
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void setup() {
  /*Pins setup*/
  pinMode(ignition_sig, INPUT_PULLDOWN);
  pinMode(rtds_sig, OUTPUT);
  pinMode(br_light, OUTPUT);
  pinMode(frg,OUTPUT);
  pinMode(rfe,OUTPUT);
  pinMode(c_plus, INPUT_PULLDOWN);
//  pinMode(AD, OUTPUT);
//  pinMode(AE, OUTPUT);
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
